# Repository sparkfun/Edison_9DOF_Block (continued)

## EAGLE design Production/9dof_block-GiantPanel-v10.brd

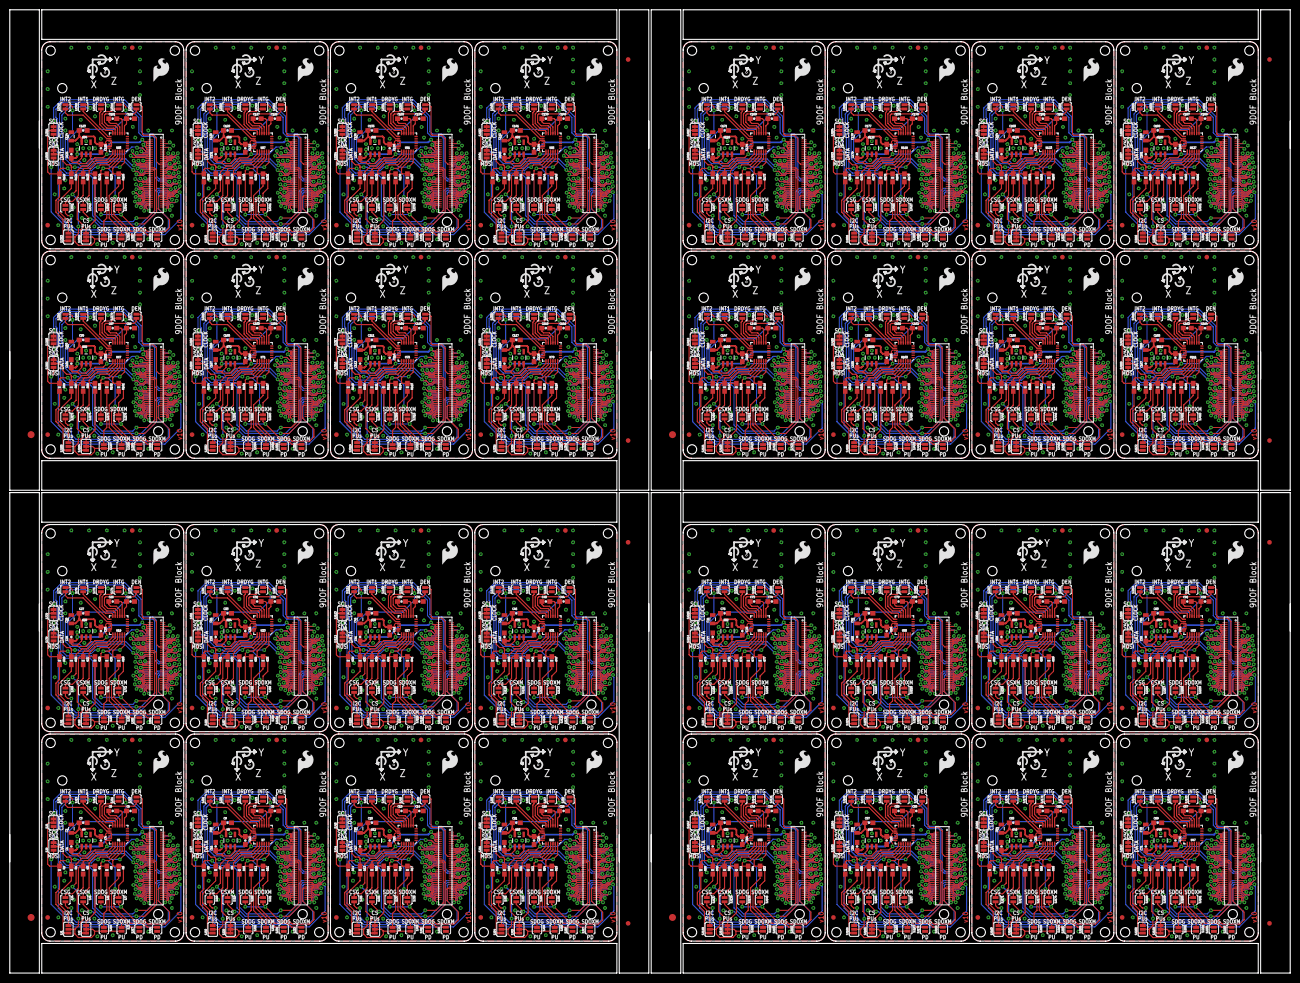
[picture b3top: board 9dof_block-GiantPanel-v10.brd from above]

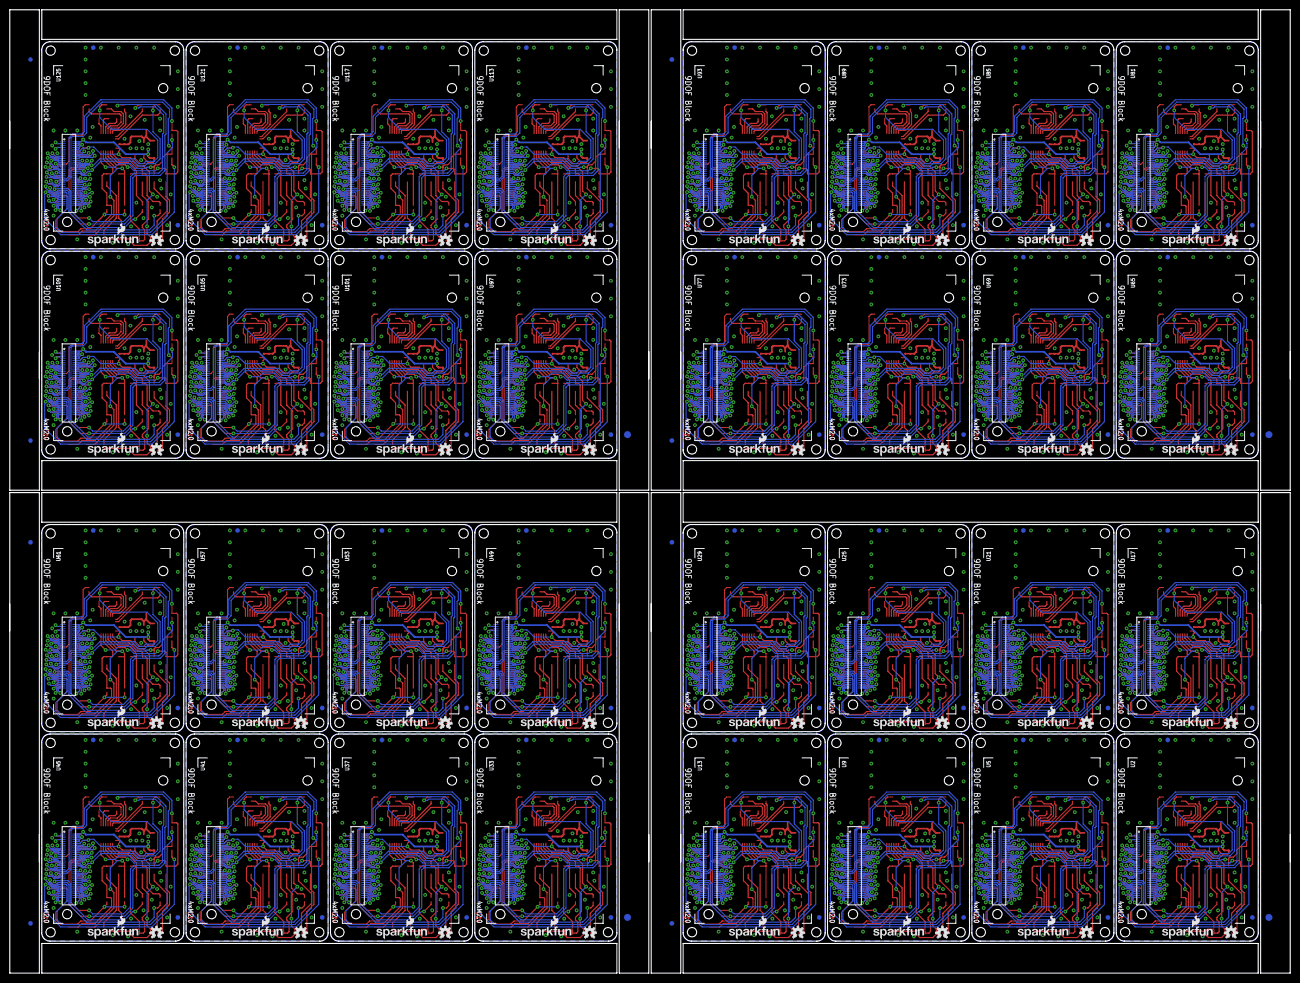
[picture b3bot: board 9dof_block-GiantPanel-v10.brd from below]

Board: 2 copper layers, 274.8 x 206.8 mm, 1304 parts (204 on the bottom side), 2528 nets.

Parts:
C1, C3, C9, C11, C15, C17, C21, C23, C27, C29, C33, C35, C39, C41, C45, C47, C51, C53, C57, C59, C63, C65, C69, C71, C75, C77, C81, C83, C87, C89, C93, C95, C99, C101, C105, C107, C111, C113, C117, C119, C123, C125, C129, C131, C135, C137, C141, C143, C147, C149, C153, C155, C159, C161, C165, C167, C171, C173, C177, C179, C183, C185, C189, C191: 1.0uF; 0603-CAP
C2, C10, C16, C22, C28, C34, C40, C46, C52, C58, C64, C70, C76, C82, C88, C94, C100, C106, C112, C118, C124, C130, C136, C142, C148, C154, C160, C166, C172, C178, C184, C190: 10uF; 0805
C4, C12, C18, C24, C30, C36, C42, C48, C54, C60, C66, C72, C78, C84, C90, C96, C102, C108, C114, C120, C126, C132, C138, C144, C150, C156, C162, C168, C174, C180, C186, C192: 0.1uF; 0603-CAP
C5, C7, C13, C19, C25, C31, C37, C43, C49, C55, C61, C67, C73, C79, C85, C91, C97, C103, C109, C115, C121, C127, C133, C139, C145, C151, C157, C163, C169, C175, C181, C187: 0.22uF; 0603-CAP
C6, C8, C14, C20, C26, C32, C38, C44, C50, C56, C62, C68, C74, C80, C86, C92, C98, C104, C110, C116, C122, C128, C134, C140, C146, C152, C158, C164, C170, C176, C182, C188: 4.7uF; 0603-CAP
E$1, E$2, E$9, E$10, E$15, E$16, E$21, E$22: FIDUCIAL-1.5X3
E$3, E$4, E$5, E$6, E$7, E$8, E$11, E$12, E$13, E$14, E$17, E$18, E$19, E$20, E$23, E$24: FIDUCIAL-1X2
FID1, FID2, FID3, FID4, FID5, FID6, FID7, FID8, FID9, FID10, FID11, FID12, FID13, FID14, FID15, FID16, FID17, FID18, FID19, FID20, FID21, FID22, FID23, FID24, FID25, FID26, FID27, FID28, FID29, FID30, FID31, FID32, FID33, FID34, FID35, FID36, FID37, FID38, FID39, FID40, FID41, FID42, FID43, FID44, FID45, FID46, FID47, FID48, FID49, FID50, FID51, FID52, FID53, FID54, FID55, FID56, FID57, FID58, FID59, FID60, FID61, FID62, FID63, FID64, FID65, FID66, FID67, FID68, FID69, FID70, FID71, FID72, FID73, FID74, FID75, FID76, FID77, FID78, FID79, FID80, FID81, FID82, FID83, FID84, FID85, FID86, FID87, FID88, FID89, FID90, FID91, FID92, FID93, FID94, FID95, FID96, FID97, FID98, FID99, FID100, FID101, FID102, FID103, FID104, FID105, FID106, FID107, FID108, FID109, FID110, FID111, FID112, FID113, FID114, FID115, FID116, FID117, FID118, FID119, FID120, FID121, FID122, FID123, FID124, FID125, FID126, FID127, FID128: FIDUCIAL1X2; FIDUCIAL-1X2
LOGO1, LOGO6, LOGO9, LOGO12, LOGO15, LOGO18, LOGO21, LOGO24, LOGO27, LOGO30, LOGO33, LOGO36, LOGO39, LOGO42, LOGO45, LOGO48, LOGO51, LOGO54, LOGO57, LOGO60, LOGO63, LOGO66, LOGO69, LOGO72, LOGO75, LOGO78, LOGO81, LOGO84, LOGO87, LOGO90, LOGO93, LOGO96: SFE_LOGO_FLAME.2_INCH; SFE_LOGO_FLAME_.2
LOGO2, LOGO4, LOGO7, LOGO10, LOGO13, LOGO16, LOGO19, LOGO22, LOGO25, LOGO28, LOGO31, LOGO34, LOGO37, LOGO40, LOGO43, LOGO46, LOGO49, LOGO52, LOGO55, LOGO58, LOGO61, LOGO64, LOGO67, LOGO70, LOGO73, LOGO76, LOGO79, LOGO82, LOGO85, LOGO88, LOGO91, LOGO94: OSHW-LOGOS; OSHW-LOGO-S
LOGO3, LOGO5, LOGO8, LOGO11, LOGO14, LOGO17, LOGO20, LOGO23, LOGO26, LOGO29, LOGO32, LOGO35, LOGO38, LOGO41, LOGO44, LOGO47, LOGO50, LOGO53, LOGO56, LOGO59, LOGO62, LOGO65, LOGO68, LOGO71, LOGO74, LOGO77, LOGO80, LOGO83, LOGO86, LOGO89, LOGO92, LOGO95: SFE_LOGO_NAME_FLAME.1_INCH; SFE_LOGO_NAME_FLAME_.1
R1, R2, R7, R8, R13, R14, R19, R20, R25, R26, R31, R32, R37, R38, R43, R44, R49, R50, R55, R56, R61, R62, R67, R68, R73, R74, R79, R80, R85, R86, R91, R92, R97, R98, R103, R104, R109, R110, R115, R116, R121, R122, R127, R128, R133, R134, R139, R140, R145, R146, R151, R152, R157, R158, R163, R164, R169, R170, R175, R176, R181, R182, R187, R188: 10K; 0603-RES
R3, R4, R5, R6, R9, R10, R11, R12, R15, R16, R17, R18, R21, R22, R23, R24, R27, R28, R29, R30, R33, R34, R35, R36, R39, R40, R41, R42, R45, R46, R47, R48, R51, R52, R53, R54, R57, R58, R59, R60, R63, R64, R65, R66, R69, R70, R71, R72, R75, R76, R77, R78, R81, R82, R83, R84, R87, R88, R89, R90, R93, R94, R95, R96, R99, R100, R101, R102, R105, R106, R107, R108, R111, R112, R113, R114, R117, R118, R119, R120, R123, R124, R125, R126, R129, R130, R131, R132, R135, R136, R137, R138, R141, R142, R143, R144, R147, R148, R149, R150, R153, R154, R155, R156, R159, R160, R161, R162, R165, R166, R167, R168, R171, R172, R173, R174, R177, R178, R179, R180, R183, R184, R185, R186, R189, R190, R191, R192: 10k; 0603-RES
SJ1, SJ30, SJ47, SJ64, SJ81, SJ98, SJ115, SJ132, SJ149, SJ166, SJ183, SJ200, SJ217, SJ234, SJ251, SJ268, SJ285, SJ302, SJ319, SJ336, SJ353, SJ370, SJ387, SJ404, SJ421, SJ438, SJ455, SJ472, SJ489, SJ506, SJ523, SJ540: JUMPER-PAD-3-NOYES_SILK; PAD-JUMPER-3-NO_YES_SILK
SJ2, SJ29, SJ46, SJ63, SJ80, SJ97, SJ114, SJ131, SJ148, SJ165, SJ182, SJ199, SJ216, SJ233, SJ250, SJ267, SJ284, SJ301, SJ318, SJ335, SJ352, SJ369, SJ386, SJ403, SJ420, SJ437, SJ454, SJ471, SJ488, SJ505, SJ522, SJ539: PAD-JUMPER-3-3OF3_NC_BY_TRACE_YES_SILK_FULL_BOX
SJ3, SJ15, SJ31, SJ32, SJ48, SJ49, SJ65, SJ66, SJ82, SJ83, SJ99, SJ100, SJ116, SJ117, SJ133, SJ134, SJ150, SJ151, SJ167, SJ168, SJ184, SJ185, SJ201, SJ202, SJ218, SJ219, SJ235, SJ236, SJ252, SJ253, SJ269, SJ270, SJ286, SJ287, SJ303, SJ304, SJ320, SJ321, SJ337, SJ338, SJ354, SJ355, SJ371, SJ372, SJ388, SJ389, SJ405, SJ406, SJ422, SJ423, SJ439, SJ440, SJ456, SJ457, SJ473, SJ474, SJ490, SJ491, SJ507, SJ508, SJ524, SJ525, SJ541, SJ542: JUMPER-PAD-2-NC_BY_PASTE; PAD-JUMPER-2-NC_BY_PASTE_YES_SILK
SJ4, SJ5, SJ6, SJ7, SJ10, SJ11, SJ12, SJ13, SJ14, SJ16, SJ17, SJ18, SJ19, SJ20, SJ21, SJ22, SJ23, SJ24, SJ25, SJ26, SJ33, SJ34, SJ35, SJ36, SJ37, SJ38, SJ39, SJ40, SJ41, SJ42, SJ43, SJ50, SJ51, SJ52, SJ53, SJ54, SJ55, SJ56, SJ57, SJ58, SJ59, SJ60, SJ67, SJ68, SJ69, SJ70, SJ71, SJ72, SJ73, SJ74, SJ75, SJ76, SJ77, SJ84, SJ85, SJ86, SJ87, SJ88, SJ89, SJ90, SJ91, SJ92, SJ93, SJ94, SJ101, SJ102, SJ103, SJ104, SJ105, SJ106, SJ107, SJ108, SJ109, SJ110, SJ111, SJ118, SJ119, SJ120, SJ121, SJ122, SJ123, SJ124, SJ125, SJ126, SJ127, SJ128, SJ135, SJ136, SJ137, SJ138, SJ139, SJ140, SJ141, SJ142, SJ143, SJ144, SJ145, SJ152, SJ153, SJ154, SJ155, SJ156, SJ157, SJ158, SJ159, SJ160, SJ161, SJ162, SJ169, SJ170, SJ171, SJ172, SJ173, SJ174, SJ175, SJ176, SJ177, SJ178, SJ179, SJ186, SJ187, SJ188, SJ189, SJ190, SJ191, SJ192, SJ193, SJ194, SJ195, SJ196, SJ203, SJ204, SJ205, SJ206, SJ207, SJ208, SJ209, SJ210, SJ211, SJ212, SJ213, SJ220, SJ221, SJ222, SJ223, SJ224, SJ225, SJ226, SJ227, SJ228, SJ229, SJ230, SJ237, SJ238, SJ239, SJ240, SJ241, SJ242, SJ243, SJ244, SJ245, SJ246, SJ247, SJ254, SJ255, SJ256, SJ257, SJ258, SJ259, SJ260, SJ261, SJ262, SJ263, SJ264, SJ271, SJ272, SJ273, SJ274, SJ275, SJ276, SJ277, SJ278, SJ279, SJ280, SJ281, SJ288, SJ289, SJ290, SJ291, SJ292, SJ293, SJ294, SJ295, SJ296, SJ297, SJ298, SJ305, SJ306, SJ307, SJ308, SJ309, SJ310, SJ311, SJ312, SJ313, SJ314, SJ315, SJ322, SJ323, SJ324, SJ325, SJ326, SJ327, SJ328, SJ329, SJ330, SJ331, SJ332, SJ339, SJ340, SJ341, SJ342, SJ343, SJ344, SJ345, SJ346, SJ347, SJ348, SJ349, SJ356, SJ357, SJ358, SJ359, SJ360, SJ361, SJ362, SJ363, SJ364, SJ365, SJ366, SJ373, SJ374, SJ375, SJ376, SJ377, SJ378, SJ379, SJ380, SJ381, SJ382, SJ383, SJ390, SJ391, SJ392, SJ393, SJ394, SJ395, SJ396, SJ397, SJ398, SJ399, SJ400, SJ407, SJ408, SJ409, SJ410, SJ411, SJ412, SJ413, SJ414, SJ415, SJ416, SJ417, SJ424, SJ425, SJ426, SJ427, SJ428, SJ429, SJ430, SJ431, SJ432, SJ433, SJ434, SJ441, SJ442, SJ443, SJ444, SJ445, SJ446, SJ447, SJ448, SJ449, SJ450, SJ451, SJ458, SJ459, SJ460, SJ461, SJ462, SJ463, SJ464, SJ465, SJ466, SJ467, SJ468, SJ475, SJ476, SJ477, SJ478, SJ479, SJ480, SJ481, SJ482, SJ483, SJ484, SJ485, SJ492, SJ493, SJ494, SJ495, SJ496, SJ497, SJ498, SJ499, SJ500, SJ501, SJ502, SJ509, SJ510, SJ511, SJ512, SJ513, SJ514, SJ515, SJ516, SJ517, SJ518, SJ519, SJ526, SJ527, SJ528, SJ529, SJ530, SJ531, SJ532, SJ533, SJ534, SJ535, SJ536, SJ543, SJ544: JUMPER-PAD-2-NOYES_SILK; PAD-JUMPER-2-NO_YES_SILK
SJ8, SJ9, SJ27, SJ28, SJ44, SJ45, SJ61, SJ62, SJ78, SJ79, SJ95, SJ96, SJ112, SJ113, SJ129, SJ130, SJ146, SJ147, SJ163, SJ164, SJ180, SJ181, SJ197, SJ198, SJ214, SJ215, SJ231, SJ232, SJ248, SJ249, SJ265, SJ266, SJ282, SJ283, SJ299, SJ300, SJ316, SJ317, SJ333, SJ334, SJ350, SJ351, SJ367, SJ368, SJ384, SJ385, SJ401, SJ402, SJ418, SJ419, SJ435, SJ436, SJ452, SJ453, SJ469, SJ470, SJ486, SJ487, SJ503, SJ504, SJ520, SJ521, SJ537, SJ538: JUMPER-PAD-3-2OF3_NC_BY_TRACE_SMALL; PAD-JUMPER-3-2OF3_NC_BY_TRACE_YES_SILK_FULL_BOX
U1, U7, U11, U15, U19, U23, U27, U31, U35, U39, U43, U47, U51, U55, U59, U63, U67, U71, U75, U79, U83, U87, U91, U95, U99, U103, U107, U111, U115, U119, U123, U127: LSM9DS0; LGA-24
U2, U5, U9, U13, U17, U21, U25, U29, U33, U37, U41, U45, U49, U53, U57, U61, U65, U69, U73, U77, U81, U85, U89, U93, U97, U101, U105, U109, U113, U117, U121, U125: EDISON_CONNECTOR_FULLMOUNTING_HOLES; EDISON_DAUGHTER
U3, U6, U10, U14, U18, U22, U26, U30, U34, U38, U42, U46, U50, U54, U58, U62, U66, U70, U74, U78, U82, U86, U90, U94, U98, U102, U106, U110, U114, U118, U122, U126: EDISON_CONNECTOR_FULLHEADER; DF40C-70DP-0.4(51)
U4, U8, U12, U16, U20, U24, U28, U32, U36, U40, U44, U48, U52, U56, U60, U64, U68, U72, U76, U80, U84, U88, U92, U96, U100, U104, U108, U112, U116, U120, U124, U128: MIC52053.3V; SOT23-5

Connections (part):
1.8V: SJ1.2, SJ2.2, SJ3.2, SJ15.2, U1.18, U2.12, U3.12
1.8V1: SJ29.2, SJ30.2, SJ31.2, SJ32.2, U5.12, U6.12, U7.18
1.8V2: SJ46.2, SJ47.2, SJ48.2, SJ49.2, U9.12, U10.12, U11.18
1.8V3: SJ63.2, SJ64.2, SJ65.2, SJ66.2, U13.12, U14.12, U15.18
1.8V4: SJ80.2, SJ81.2, SJ82.2, SJ83.2, U17.12, U18.12, U19.18
1.8V5: SJ97.2, SJ98.2, SJ99.2, SJ100.2, U21.12, U22.12, U23.18
1.8V6: SJ114.2, SJ115.2, SJ116.2, SJ117.2, U25.12, U26.12, U27.18
1.8V7: SJ131.2, SJ132.2, SJ133.2, SJ134.2, U29.12, U30.12, U31.18
1.8V8: SJ148.2, SJ149.2, SJ150.2, SJ151.2, U33.12, U34.12, U35.18
1.8V9: SJ165.2, SJ166.2, SJ167.2, SJ168.2, U37.12, U38.12, U39.18
1.8V10: SJ182.2, SJ183.2, SJ184.2, SJ185.2, U41.12, U42.12, U43.18
1.8V11: SJ199.2, SJ200.2, SJ201.2, SJ202.2, U45.12, U46.12, U47.18
1.8V12: SJ216.2, SJ217.2, SJ218.2, SJ219.2, U49.12, U50.12, U51.18
1.8V13: SJ233.2, SJ234.2, SJ235.2, SJ236.2, U53.12, U54.12, U55.18
1.8V14: SJ250.2, SJ251.2, SJ252.2, SJ253.2, U57.12, U58.12, U59.18
1.8V15: SJ267.2, SJ268.2, SJ269.2, SJ270.2, U61.12, U62.12, U63.18
1.8V16: SJ284.2, SJ285.2, SJ286.2, SJ287.2, U65.12, U66.12, U67.18
1.8V17: SJ301.2, SJ302.2, SJ303.2, SJ304.2, U69.12, U70.12, U71.18
1.8V18: SJ318.2, SJ319.2, SJ320.2, SJ321.2, U73.12, U74.12, U75.18
1.8V19: SJ335.2, SJ336.2, SJ337.2, SJ338.2, U77.12, U78.12, U79.18
1.8V20: SJ352.2, SJ353.2, SJ354.2, SJ355.2, U81.12, U82.12, U83.18
1.8V21: SJ369.2, SJ370.2, SJ371.2, SJ372.2, U85.12, U86.12, U87.18
1.8V22: SJ386.2, SJ387.2, SJ388.2, SJ389.2, U89.12, U90.12, U91.18
1.8V23: SJ403.2, SJ404.2, SJ405.2, SJ406.2, U93.12, U94.12, U95.18
1.8V24: SJ420.2, SJ421.2, SJ422.2, SJ423.2, U97.12, U98.12, U99.18
1.8V25: SJ437.2, SJ438.2, SJ439.2, SJ440.2, U101.12, U102.12, U103.18
1.8V26: SJ454.2, SJ455.2, SJ456.2, SJ457.2, U105.12, U106.12, U107.18
1.8V27: SJ471.2, SJ472.2, SJ473.2, SJ474.2, U109.12, U110.12, U111.18
1.8V28: SJ488.2, SJ489.2, SJ490.2, SJ491.2, U113.12, U114.12, U115.18
1.8V29: SJ505.2, SJ506.2, SJ507.2, SJ508.2, U117.12, U118.12, U119.18
1.8V30: SJ522.2, SJ523.2, SJ524.2, SJ525.2, U121.12, U122.12, U123.18
1.8V31: SJ539.2, SJ540.2, SJ541.2, SJ542.2, U125.12, U126.12, U127.18
3.3V: U2.8, U2.10, U3.8, U3.10
3.3V1: U5.8, U5.10, U6.8, U6.10
3.3V2: U9.8, U9.10, U10.8, U10.10
3.3V3: U13.8, U13.10, U14.8, U14.10
3.3V4: U17.8, U17.10, U18.8, U18.10
3.3V5: U21.8, U21.10, U22.8, U22.10
3.3V6: U25.8, U25.10, U26.8, U26.10
3.3V7: U29.8, U29.10, U30.8, U30.10
3.3V8: U33.8, U33.10, U34.8, U34.10
3.3V9: U37.8, U37.10, U38.8, U38.10
3.3V10: U41.8, U41.10, U42.8, U42.10
3.3V11: U45.8, U45.10, U46.8, U46.10
3.3V12: U49.8, U49.10, U50.8, U50.10
3.3V13: U53.8, U53.10, U54.8, U54.10
3.3V14: U57.8, U57.10, U58.8, U58.10
3.3V15: U61.8, U61.10, U62.8, U62.10
3.3V16: U65.8, U65.10, U66.8, U66.10
3.3V17: U69.8, U69.10, U70.8, U70.10
3.3V18: U73.8, U73.10, U74.8, U74.10
3.3V19: U77.8, U77.10, U78.8, U78.10
3.3V20: U81.8, U81.10, U82.8, U82.10
3.3V21: U85.8, U85.10, U86.8, U86.10
3.3V22: U89.8, U89.10, U90.8, U90.10
3.3V23: U93.8, U93.10, U94.8, U94.10
3.3V24: U97.8, U97.10, U98.8, U98.10
3.3V25: U101.8, U101.10, U102.8, U102.10
3.3V26: U105.8, U105.10, U106.8, U106.10
3.3V27: U109.8, U109.10, U110.8, U110.10
3.3V28: U113.8, U113.10, U114.8, U114.10
3.3V29: U117.8, U117.10, U118.8, U118.10
3.3V30: U121.8, U121.10, U122.8, U122.10
3.3V31: U125.8, U125.10, U126.8, U126.10
3.3V_LOCAL: C2.1, C3.1, C4.1, U1.15, U1.16, U1.17, U4.5
3.3V_LOCAL1: C9.1, C10.1, C12.1, U7.15, U7.16, U7.17, U8.5
3.3V_LOCAL2: C15.1, C16.1, C18.1, U11.15, U11.16, U11.17, U12.5
3.3V_LOCAL3: C21.1, C22.1, C24.1, U15.15, U15.16, U15.17, U16.5
3.3V_LOCAL4: C27.1, C28.1, C30.1, U19.15, U19.16, U19.17, U20.5
3.3V_LOCAL5: C33.1, C34.1, C36.1, U23.15, U23.16, U23.17, U24.5
3.3V_LOCAL6: C39.1, C40.1, C42.1, U27.15, U27.16, U27.17, U28.5
3.3V_LOCAL7: C45.1, C46.1, C48.1, U31.15, U31.16, U31.17, U32.5
3.3V_LOCAL8: C51.1, C52.1, C54.1, U35.15, U35.16, U35.17, U36.5
3.3V_LOCAL9: C57.1, C58.1, C60.1, U39.15, U39.16, U39.17, U40.5
3.3V_LOCAL10: C63.1, C64.1, C66.1, U43.15, U43.16, U43.17, U44.5
3.3V_LOCAL11: C69.1, C70.1, C72.1, U47.15, U47.16, U47.17, U48.5
3.3V_LOCAL12: C75.1, C76.1, C78.1, U51.15, U51.16, U51.17, U52.5
3.3V_LOCAL13: C81.1, C82.1, C84.1, U55.15, U55.16, U55.17, U56.5
3.3V_LOCAL14: C87.1, C88.1, C90.1, U59.15, U59.16, U59.17, U60.5
3.3V_LOCAL15: C93.1, C94.1, C96.1, U63.15, U63.16, U63.17, U64.5
3.3V_LOCAL16: C99.1, C100.1, C102.1, U67.15, U67.16, U67.17, U68.5
3.3V_LOCAL17: C105.1, C106.1, C108.1, U71.15, U71.16, U71.17, U72.5
3.3V_LOCAL18: C111.1, C112.1, C114.1, U75.15, U75.16, U75.17, U76.5
3.3V_LOCAL19: C117.1, C118.1, C120.1, U79.15, U79.16, U79.17, U80.5
3.3V_LOCAL20: C123.1, C124.1, C126.1, U83.15, U83.16, U83.17, U84.5
3.3V_LOCAL21: C129.1, C130.1, C132.1, U87.15, U87.16, U87.17, U88.5
3.3V_LOCAL22: C135.1, C136.1, C138.1, U91.15, U91.16, U91.17, U92.5
3.3V_LOCAL23: C141.1, C142.1, C144.1, U95.15, U95.16, U95.17, U96.5
3.3V_LOCAL24: C147.1, C148.1, C150.1, U99.15, U99.16, U99.17, U100.5
3.3V_LOCAL25: C153.1, C154.1, C156.1, U103.15, U103.16, U103.17, U104.5
3.3V_LOCAL26: C159.1, C160.1, C162.1, U107.15, U107.16, U107.17, U108.5
3.3V_LOCAL27: C165.1, C166.1, C168.1, U111.15, U111.16, U111.17, U112.5
3.3V_LOCAL28: C171.1, C172.1, C174.1, U115.15, U115.16, U115.17, U116.5
3.3V_LOCAL29: C177.1, C178.1, C180.1, U119.15, U119.16, U119.17, U120.5
3.3V_LOCAL30: C183.1, C184.1, C186.1, U123.15, U123.16, U123.17, U124.5
3.3V_LOCAL31: C189.1, C190.1, C192.1, U127.15, U127.16, U127.17, U128.5
CS_G: R3.1, SJ4.1, U1.19
CS_G1: R9.1, SJ18.1, U7.19
CS_G2: R15.1, SJ35.1, U11.19
CS_G3: R21.1, SJ52.1, U15.19
CS_G4: R27.1, SJ69.1, U19.19
CS_G5: R33.1, SJ86.1, U23.19
CS_G6: R39.1, SJ103.1, U27.19
CS_G7: R45.1, SJ120.1, U31.19
CS_G8: R51.1, SJ137.1, U35.19
CS_G9: R57.1, SJ154.1, U39.19
CS_G10: R63.1, SJ171.1, U43.19
CS_G11: R69.1, SJ188.1, U47.19
CS_G12: R75.1, SJ205.1, U51.19
CS_G13: R81.1, SJ222.1, U55.19
CS_G14: R87.1, SJ239.1, U59.19
CS_G15: R93.1, SJ256.1, U63.19
CS_G16: R99.1, SJ273.1, U67.19
CS_G17: R105.1, SJ290.1, U71.19
CS_G18: R111.1, SJ307.1, U75.19
CS_G19: R117.1, SJ324.1, U79.19
CS_G20: R123.1, SJ341.1, U83.19
CS_G21: R129.1, SJ358.1, U87.19
CS_G22: R135.1, SJ375.1, U91.19
CS_G23: R141.1, SJ392.1, U95.19
CS_G24: R147.1, SJ409.1, U99.19
CS_G25: R153.1, SJ426.1, U103.19
CS_G26: R159.1, SJ443.1, U107.19
CS_G27: R165.1, SJ460.1, U111.19
CS_G28: R171.1, SJ477.1, U115.19
CS_G29: R177.1, SJ494.1, U119.19
CS_G30: R183.1, SJ511.1, U123.19
CS_G31: R189.1, SJ528.1, U127.19
CS_XM: R4.1, SJ5.1, U1.20
CS_XM1: R10.1, SJ19.1, U7.20
CS_XM2: R16.1, SJ36.1, U11.20
CS_XM3: R22.1, SJ53.1, U15.20
CS_XM4: R28.1, SJ70.1, U19.20
CS_XM5: R34.1, SJ87.1, U23.20
CS_XM6: R40.1, SJ104.1, U27.20
CS_XM7: R46.1, SJ121.1, U31.20
CS_XM8: R52.1, SJ138.1, U35.20
CS_XM9: R58.1, SJ155.1, U39.20
CS_XM10: R64.1, SJ172.1, U43.20
CS_XM11: R70.1, SJ189.1, U47.20
CS_XM12: R76.1, SJ206.1, U51.20
CS_XM13: R82.1, SJ223.1, U55.20
CS_XM14: R88.1, SJ240.1, U59.20
CS_XM15: R94.1, SJ257.1, U63.20
CS_XM16: R100.1, SJ274.1, U67.20
CS_XM17: R106.1, SJ291.1, U71.20
CS_XM18: R112.1, SJ308.1, U75.20
CS_XM19: R118.1, SJ325.1, U79.20
CS_XM20: R124.1, SJ342.1, U83.20
CS_XM21: R130.1, SJ359.1, U87.20
CS_XM22: R136.1, SJ376.1, U91.20
CS_XM23: R142.1, SJ393.1, U95.20
CS_XM24: R148.1, SJ410.1, U99.20
CS_XM25: R154.1, SJ427.1, U103.20
CS_XM26: R160.1, SJ444.1, U107.20
CS_XM27: R166.1, SJ461.1, U111.20
CS_XM28: R172.1, SJ478.1, U115.20
CS_XM29: R178.1, SJ495.1, U119.20
CS_XM30: R184.1, SJ512.1, U123.20
CS_XM31: R190.1, SJ529.1, U127.20
DCIN: U2.14, U3.14
DCIN1: U5.14, U6.14
DCIN2: U9.14, U10.14
DCIN3: U13.14, U14.14
DCIN4: U17.14, U18.14
DCIN5: U21.14, U22.14
DCIN6: U25.14, U26.14
DCIN7: U29.14, U30.14
DCIN8: U33.14, U34.14
DCIN9: U37.14, U38.14
DCIN10: U41.14, U42.14
DCIN11: U45.14, U46.14
DCIN12: U49.14, U50.14
DCIN13: U53.14, U54.14
DCIN14: U57.14, U58.14
DCIN15: U61.14, U62.14
DCIN16: U65.14, U66.14
DCIN17: U69.14, U70.14
DCIN18: U73.14, U74.14
DCIN19: U77.14, U78.14
DCIN20: U81.14, U82.14
DCIN21: U85.14, U86.14
DCIN22: U89.14, U90.14
DCIN23: U93.14, U94.14
DCIN24: U97.14, U98.14
DCIN25: U101.14, U102.14
DCIN26: U105.14, U106.14
DCIN27: U109.14, U110.14
DCIN28: U113.14, U114.14
DCIN29: U117.14, U118.14
DCIN30: U121.14, U122.14
DCIN31: U125.14, U126.14
DEN_G: SJ10.1, U1.10
DEN_G1: SJ22.1, U7.10
DEN_G2: SJ39.1, U11.10
DEN_G3: SJ56.1, U15.10
DEN_G4: SJ73.1, U19.10
DEN_G5: SJ90.1, U23.10
DEN_G6: SJ107.1, U27.10
DEN_G7: SJ124.1, U31.10
DEN_G8: SJ141.1, U35.10
DEN_G9: SJ158.1, U39.10
DEN_G10: SJ175.1, U43.10
DEN_G11: SJ192.1, U47.10
DEN_G12: SJ209.1, U51.10
DEN_G13: SJ226.1, U55.10
DEN_G14: SJ243.1, U59.10
DEN_G15: SJ260.1, U63.10
DEN_G16: SJ277.1, U67.10
DEN_G17: SJ294.1, U71.10
DEN_G18: SJ311.1, U75.10
DEN_G19: SJ328.1, U79.10
DEN_G20: SJ345.1, U83.10
DEN_G21: SJ362.1, U87.10
DEN_G22: SJ379.1, U91.10
DEN_G23: SJ396.1, U95.10
DEN_G24: SJ413.1, U99.10
DEN_G25: SJ430.1, U103.10
DEN_G26: SJ447.1, U107.10
DEN_G27: SJ464.1, U111.10
DEN_G28: SJ481.1, U115.10
DEN_G29: SJ498.1, U119.10
DEN_G30: SJ515.1, U123.10
DEN_G31: SJ532.1, U127.10
DRDY_G: SJ12.1, U1.12
DRDY_G1: SJ24.1, U7.12
DRDY_G2: SJ41.1, U11.12
DRDY_G3: SJ58.1, U15.12
DRDY_G4: SJ75.1, U19.12
DRDY_G5: SJ92.1, U23.12
DRDY_G6: SJ109.1, U27.12
DRDY_G7: SJ126.1, U31.12
DRDY_G8: SJ143.1, U35.12
DRDY_G9: SJ160.1, U39.12
DRDY_G10: SJ177.1, U43.12
DRDY_G11: SJ194.1, U47.12
DRDY_G12: SJ211.1, U51.12
DRDY_G13: SJ228.1, U55.12
DRDY_G14: SJ245.1, U59.12
DRDY_G15: SJ262.1, U63.12
DRDY_G16: SJ279.1, U67.12
DRDY_G17: SJ296.1, U71.12
DRDY_G18: SJ313.1, U75.12
DRDY_G19: SJ330.1, U79.12
DRDY_G20: SJ347.1, U83.12
DRDY_G21: SJ364.1, U87.12
DRDY_G22: SJ381.1, U91.12
DRDY_G23: SJ398.1, U95.12
DRDY_G24: SJ415.1, U99.12
DRDY_G25: SJ432.1, U103.12
DRDY_G26: SJ449.1, U107.12
DRDY_G27: SJ466.1, U111.12
DRDY_G28: SJ483.1, U115.12
DRDY_G29: SJ500.1, U119.12
DRDY_G30: SJ517.1, U123.12
DRDY_G31: SJ534.1, U127.12
FAULT: U2.19, U3.19
FAULT1: U5.19, U6.19
FAULT2: U9.19, U10.19
FAULT3: U13.19, U14.19
FAULT4: U17.19, U18.19
FAULT5: U21.19, U22.19
FAULT6: U25.19, U26.19
FAULT7: U29.19, U30.19
FAULT8: U33.19, U34.19
FAULT9: U37.19, U38.19
FAULT10: U41.19, U42.19
FAULT11: U45.19, U46.19
FAULT12: U49.19, U50.19
FAULT13: U53.19, U54.19
FAULT14: U57.19, U58.19
FAULT15: U61.19, U62.19
FAULT16: U65.19, U66.19
FAULT17: U69.19, U70.19
FAULT18: U73.19, U74.19
FAULT19: U77.19, U78.19
FAULT20: U81.19, U82.19
FAULT21: U85.19, U86.19
FAULT22: U89.19, U90.19
FAULT23: U93.19, U94.19
FAULT24: U97.19, U98.19
FAULT25: U101.19, U102.19
FAULT26: U105.19, U106.19
FAULT27: U109.19, U110.19
FAULT28: U113.19, U114.19
FAULT29: U117.19, U118.19
FAULT30: U121.19, U122.19
FAULT31: U125.19, U126.19
FW_RCVR: U2.69, U3.69
FW_RCVR1: U5.69, U6.69
FW_RCVR2: U9.69, U10.69
FW_RCVR3: U13.69, U14.69
FW_RCVR4: U17.69, U18.69
FW_RCVR5: U21.69, U22.69
FW_RCVR6: U25.69, U26.69
FW_RCVR7: U29.69, U30.69
FW_RCVR8: U33.69, U34.69
FW_RCVR9: U37.69, U38.69
FW_RCVR10: U41.69, U42.69
FW_RCVR11: U45.69, U46.69
FW_RCVR12: U49.69, U50.69
FW_RCVR13: U53.69, U54.69
FW_RCVR14: U57.69, U58.69
FW_RCVR15: U61.69, U62.69
FW_RCVR16: U65.69, U66.69
FW_RCVR17: U69.69, U70.69
FW_RCVR18: U73.69, U74.69
FW_RCVR19: U77.69, U78.69
FW_RCVR20: U81.69, U82.69
FW_RCVR21: U85.69, U86.69
FW_RCVR22: U89.69, U90.69
FW_RCVR23: U93.69, U94.69
FW_RCVR24: U97.69, U98.69
FW_RCVR25: U101.69, U102.69
FW_RCVR26: U105.69, U106.69
FW_RCVR27: U109.69, U110.69
FW_RCVR28: U113.69, U114.69
FW_RCVR29: U117.69, U118.69
FW_RCVR30: U121.69, U122.69
FW_RCVR31: U125.69, U126.69
GND: C1.2, C2.2, C3.2, C4.2, C6.2, SJ16.1, SJ17.1, U1.2, U1.3, U1.4, U1.5, U1.6, U2.1, U2.5, U2.9, U2.11, U2.13, U2.15, U3.1, U3.5, U3.9, U3.11, U3.13, U3.15, U4.2
GND1: C8.2, C9.2, C10.2, C11.2, C12.2, SJ33.1, SJ34.1, U5.1, U5.5, U5.9, U5.11, U5.13, U5.15, U6.1, U6.5, U6.9, U6.11, U6.13, U6.15, U7.2, U7.3, U7.4, U7.5, U7.6, U8.2
GND2: C14.2, C15.2, C16.2, C17.2, C18.2, SJ50.1, SJ51.1, U9.1, U9.5, U9.9, U9.11, U9.13, U9.15, U10.1, U10.5, U10.9, U10.11, U10.13, U10.15, U11.2, U11.3, U11.4, U11.5, U11.6, U12.2
GND3: C20.2, C21.2, C22.2, C23.2, C24.2, SJ67.1, SJ68.1, U13.1, U13.5, U13.9, U13.11, U13.13, U13.15, U14.1, U14.5, U14.9, U14.11, U14.13, U14.15, U15.2, U15.3, U15.4, U15.5, U15.6, U16.2
GND4: C26.2, C27.2, C28.2, C29.2, C30.2, SJ84.1, SJ85.1, U17.1, U17.5, U17.9, U17.11, U17.13, U17.15, U18.1, U18.5, U18.9, U18.11, U18.13, U18.15, U19.2, U19.3, U19.4, U19.5, U19.6, U20.2
GND5: C32.2, C33.2, C34.2, C35.2, C36.2, SJ101.1, SJ102.1, U21.1, U21.5, U21.9, U21.11, U21.13, U21.15, U22.1, U22.5, U22.9, U22.11, U22.13, U22.15, U23.2, U23.3, U23.4, U23.5, U23.6, U24.2
GND6: C38.2, C39.2, C40.2, C41.2, C42.2, SJ118.1, SJ119.1, U25.1, U25.5, U25.9, U25.11, U25.13, U25.15, U26.1, U26.5, U26.9, U26.11, U26.13, U26.15, U27.2, U27.3, U27.4, U27.5, U27.6, U28.2
GND7: C44.2, C45.2, C46.2, C47.2, C48.2, SJ135.1, SJ136.1, U29.1, U29.5, U29.9, U29.11, U29.13, U29.15, U30.1, U30.5, U30.9, U30.11, U30.13, U30.15, U31.2, U31.3, U31.4, U31.5, U31.6, U32.2
GND8: C50.2, C51.2, C52.2, C53.2, C54.2, SJ152.1, SJ153.1, U33.1, U33.5, U33.9, U33.11, U33.13, U33.15, U34.1, U34.5, U34.9, U34.11, U34.13, U34.15, U35.2, U35.3, U35.4, U35.5, U35.6, U36.2
GND9: C56.2, C57.2, C58.2, C59.2, C60.2, SJ169.1, SJ170.1, U37.1, U37.5, U37.9, U37.11, U37.13, U37.15, U38.1, U38.5, U38.9, U38.11, U38.13, U38.15, U39.2, U39.3, U39.4, U39.5, U39.6, U40.2
GND10: C62.2, C63.2, C64.2, C65.2, C66.2, SJ186.1, SJ187.1, U41.1, U41.5, U41.9, U41.11, U41.13, U41.15, U42.1, U42.5, U42.9, U42.11, U42.13, U42.15, U43.2, U43.3, U43.4, U43.5, U43.6, U44.2
GND11: C68.2, C69.2, C70.2, C71.2, C72.2, SJ203.1, SJ204.1, U45.1, U45.5, U45.9, U45.11, U45.13, U45.15, U46.1, U46.5, U46.9, U46.11, U46.13, U46.15, U47.2, U47.3, U47.4, U47.5, U47.6, U48.2
GND12: C74.2, C75.2, C76.2, C77.2, C78.2, SJ220.1, SJ221.1, U49.1, U49.5, U49.9, U49.11, U49.13, U49.15, U50.1, U50.5, U50.9, U50.11, U50.13, U50.15, U51.2, U51.3, U51.4, U51.5, U51.6, U52.2
GND13: C80.2, C81.2, C82.2, C83.2, C84.2, SJ237.1, SJ238.1, U53.1, U53.5, U53.9, U53.11, U53.13, U53.15, U54.1, U54.5, U54.9, U54.11, U54.13, U54.15, U55.2, U55.3, U55.4, U55.5, U55.6, U56.2
GND14: C86.2, C87.2, C88.2, C89.2, C90.2, SJ254.1, SJ255.1, U57.1, U57.5, U57.9, U57.11, U57.13, U57.15, U58.1, U58.5, U58.9, U58.11, U58.13, U58.15, U59.2, U59.3, U59.4, U59.5, U59.6, U60.2
GND15: C92.2, C93.2, C94.2, C95.2, C96.2, SJ271.1, SJ272.1, U61.1, U61.5, U61.9, U61.11, U61.13, U61.15, U62.1, U62.5, U62.9, U62.11, U62.13, U62.15, U63.2, U63.3, U63.4, U63.5, U63.6, U64.2
GND16: C98.2, C99.2, C100.2, C101.2, C102.2, SJ288.1, SJ289.1, U65.1, U65.5, U65.9, U65.11, U65.13, U65.15, U66.1, U66.5, U66.9, U66.11, U66.13, U66.15, U67.2, U67.3, U67.4, U67.5, U67.6, U68.2
GND17: C104.2, C105.2, C106.2, C107.2, C108.2, SJ305.1, SJ306.1, U69.1, U69.5, U69.9, U69.11, U69.13, U69.15, U70.1, U70.5, U70.9, U70.11, U70.13, U70.15, U71.2, U71.3, U71.4, U71.5, U71.6, U72.2
GND18: C110.2, C111.2, C112.2, C113.2, C114.2, SJ322.1, SJ323.1, U73.1, U73.5, U73.9, U73.11, U73.13, U73.15, U74.1, U74.5, U74.9, U74.11, U74.13, U74.15, U75.2, U75.3, U75.4, U75.5, U75.6, U76.2
GND19: C116.2, C117.2, C118.2, C119.2, C120.2, SJ339.1, SJ340.1, U77.1, U77.5, U77.9, U77.11, U77.13, U77.15, U78.1, U78.5, U78.9, U78.11, U78.13, U78.15, U79.2, U79.3, U79.4, U79.5, U79.6, U80.2
GND20: C122.2, C123.2, C124.2, C125.2, C126.2, SJ356.1, SJ357.1, U81.1, U81.5, U81.9, U81.11, U81.13, U81.15, U82.1, U82.5, U82.9, U82.11, U82.13, U82.15, U83.2, U83.3, U83.4, U83.5, U83.6, U84.2
GND21: C128.2, C129.2, C130.2, C131.2, C132.2, SJ373.1, SJ374.1, U85.1, U85.5, U85.9, U85.11, U85.13, U85.15, U86.1, U86.5, U86.9, U86.11, U86.13, U86.15, U87.2, U87.3, U87.4, U87.5, U87.6, U88.2
GND22: C134.2, C135.2, C136.2, C137.2, C138.2, SJ390.1, SJ391.1, U89.1, U89.5, U89.9, U89.11, U89.13, U89.15, U90.1, U90.5, U90.9, U90.11, U90.13, U90.15, U91.2, U91.3, U91.4, U91.5, U91.6, U92.2
GND23: C140.2, C141.2, C142.2, C143.2, C144.2, SJ407.1, SJ408.1, U93.1, U93.5, U93.9, U93.11, U93.13, U93.15, U94.1, U94.5, U94.9, U94.11, U94.13, U94.15, U95.2, U95.3, U95.4, U95.5, U95.6, U96.2
GND24: C146.2, C147.2, C148.2, C149.2, C150.2, SJ424.1, SJ425.1, U97.1, U97.5, U97.9, U97.11, U97.13, U97.15, U98.1, U98.5, U98.9, U98.11, U98.13, U98.15, U99.2, U99.3, U99.4, U99.5, U99.6, U100.2
GND25: C152.2, C153.2, C154.2, C155.2, C156.2, SJ441.1, SJ442.1, U101.1, U101.5, U101.9, U101.11, U101.13, U101.15, U102.1, U102.5, U102.9, U102.11, U102.13, U102.15, U103.2, U103.3, U103.4, U103.5, U103.6, U104.2
GND26: C158.2, C159.2, C160.2, C161.2, C162.2, SJ458.1, SJ459.1, U105.1, U105.5, U105.9, U105.11, U105.13, U105.15, U106.1, U106.5, U106.9, U106.11, U106.13, U106.15, U107.2, U107.3, U107.4, U107.5, U107.6, U108.2
GND27: C164.2, C165.2, C166.2, C167.2, C168.2, SJ475.1, SJ476.1, U109.1, U109.5, U109.9, U109.11, U109.13, U109.15, U110.1, U110.5, U110.9, U110.11, U110.13, U110.15, U111.2, U111.3, U111.4, U111.5, U111.6, U112.2
GND28: C170.2, C171.2, C172.2, C173.2, C174.2, SJ492.1, SJ493.1, U113.1, U113.5, U113.9, U113.11, U113.13, U113.15, U114.1, U114.5, U114.9, U114.11, U114.13, U114.15, U115.2, U115.3, U115.4, U115.5, U115.6, U116.2
GND29: C176.2, C177.2, C178.2, C179.2, C180.2, SJ509.1, SJ510.1, U117.1, U117.5, U117.9, U117.11, U117.13, U117.15, U118.1, U118.5, U118.9, U118.11, U118.13, U118.15, U119.2, U119.3, U119.4, U119.5, U119.6, U120.2
GND30: C182.2, C183.2, C184.2, C185.2, C186.2, SJ526.1, SJ527.1, U121.1, U121.5, U121.9, U121.11, U121.13, U121.15, U122.1, U122.5, U122.9, U122.11, U122.13, U122.15, U123.2, U123.3, U123.4, U123.5, U123.6, U124.2
GND31: C188.2, C189.2, C190.2, C191.2, C192.2, SJ543.1, SJ544.1, U125.1, U125.5, U125.9, U125.11, U125.13, U125.15, U126.1, U126.5, U126.9, U126.11, U126.13, U126.15, U127.2, U127.3, U127.4, U127.5, U127.6, U128.2
GP1: U5.48, U6.48
GP2: U5.42, U6.42
GP3: SJ26.2, U5.34, U6.34
GP4: SJ25.2, U5.32, U6.32
GP5: SJ24.2, U5.30, U6.30
GP6: SJ23.2, U5.28, U6.28
GP7: U5.26, U6.26
GP8: SJ22.2, U5.25, U6.25
GP9: U5.24, U6.24
GP10: U9.48, U10.48
GP11: U9.42, U10.42
GP12: SJ43.2, U9.34, U10.34
GP12_PWM0: U2.35, U3.35
GP12_PWM1: U5.35, U6.35
GP12_PWM2: U9.35, U10.35
GP12_PWM3: U13.35, U14.35
GP12_PWM4: U17.35, U18.35
GP12_PWM5: U21.35, U22.35
GP12_PWM6: U25.35, U26.35
GP12_PWM7: U29.35, U30.35
GP12_PWM8: U33.35, U34.35
GP12_PWM9: U37.35, U38.35
GP12_PWM10: U41.35, U42.35
GP12_PWM11: U45.35, U46.35
GP12_PWM12: U49.35, U50.35
GP12_PWM13: U53.35, U54.35
GP12_PWM14: U57.35, U58.35
GP12_PWM15: U61.35, U62.35
GP12_PWM16: U65.35, U66.35
GP12_PWM17: U69.35, U70.35
GP12_PWM18: U73.35, U74.35
GP12_PWM19: U77.35, U78.35
GP12_PWM20: U81.35, U82.35
GP12_PWM21: U85.35, U86.35
GP12_PWM22: U89.35, U90.35
GP12_PWM23: U93.35, U94.35
GP12_PWM24: U97.35, U98.35
GP12_PWM25: U101.35, U102.35
GP12_PWM26: U105.35, U106.35
GP12_PWM27: U109.35, U110.35
GP12_PWM28: U113.35, U114.35
GP12_PWM29: U117.35, U118.35
GP12_PWM30: U121.35, U122.35
GP12_PWM31: U125.35, U126.35
GP13: SJ42.2, U9.32, U10.32
GP13_PWM1: U2.33, U3.33
GP13_PWM2: U5.33, U6.33
GP13_PWM3: U9.33, U10.33
GP13_PWM4: U13.33, U14.33
GP13_PWM5: U17.33, U18.33
GP13_PWM6: U21.33, U22.33
GP13_PWM7: U25.33, U26.33
GP13_PWM8: U29.33, U30.33
GP13_PWM9: U33.33, U34.33
GP13_PWM10: U37.33, U38.33
GP13_PWM11: U41.33, U42.33
GP13_PWM12: U45.33, U46.33
GP13_PWM13: U49.33, U50.33
GP13_PWM14: U53.33, U54.33
GP13_PWM15: U57.33, U58.33
GP13_PWM16: U61.33, U62.33
GP13_PWM17: U65.33, U66.33
GP13_PWM18: U69.33, U70.33
GP13_PWM19: U73.33, U74.33
GP13_PWM20: U77.33, U78.33
GP13_PWM21: U81.33, U82.33
GP13_PWM22: U85.33, U86.33
GP13_PWM23: U89.33, U90.33
GP13_PWM24: U93.33, U94.33
GP13_PWM25: U97.33, U98.33
GP13_PWM26: U101.33, U102.33
GP13_PWM27: U105.33, U106.33
GP13_PWM28: U109.33, U110.33
GP13_PWM29: U113.33, U114.33
GP13_PWM30: U117.33, U118.33
GP13_PWM31: U121.33, U122.33
GP13_PWM32: U125.33, U126.33
GP14: U2.48, U3.48
GP15: U2.42, U3.42
GP16: SJ41.2, U9.30, U10.30
GP17: SJ40.2, U9.28, U10.28
GP18: U9.26, U10.26
GP19: SJ39.2, U9.25, U10.25
GP19_I2C_1_SCL: SJ9.3, U2.41, U3.41
GP19_I2C_1_SCL1: SJ28.3, U5.41, U6.41
GP19_I2C_1_SCL2: SJ45.3, U9.41, U10.41
GP19_I2C_1_SCL3: SJ62.3, U13.41, U14.41
GP19_I2C_1_SCL4: SJ79.3, U17.41, U18.41
GP19_I2C_1_SCL5: SJ96.3, U21.41, U22.41
GP19_I2C_1_SCL6: SJ113.3, U25.41, U26.41
GP19_I2C_1_SCL7: SJ130.3, U29.41, U30.41
GP19_I2C_1_SCL8: SJ147.3, U33.41, U34.41
GP19_I2C_1_SCL9: SJ164.3, U37.41, U38.41
GP19_I2C_1_SCL10: SJ181.3, U41.41, U42.41
GP19_I2C_1_SCL11: SJ198.3, U45.41, U46.41
GP19_I2C_1_SCL12: SJ215.3, U49.41, U50.41
GP19_I2C_1_SCL13: SJ232.3, U53.41, U54.41
GP19_I2C_1_SCL14: SJ249.3, U57.41, U58.41
GP19_I2C_1_SCL15: SJ266.3, U61.41, U62.41
GP19_I2C_1_SCL16: SJ283.3, U65.41, U66.41
GP19_I2C_1_SCL17: SJ300.3, U69.41, U70.41
GP19_I2C_1_SCL18: SJ317.3, U73.41, U74.41
GP19_I2C_1_SCL19: SJ334.3, U77.41, U78.41
GP19_I2C_1_SCL20: SJ351.3, U81.41, U82.41
GP19_I2C_1_SCL21: SJ368.3, U85.41, U86.41
GP19_I2C_1_SCL22: SJ385.3, U89.41, U90.41
GP19_I2C_1_SCL23: SJ402.3, U93.41, U94.41
GP19_I2C_1_SCL24: SJ419.3, U97.41, U98.41
GP19_I2C_1_SCL25: SJ436.3, U101.41, U102.41
GP19_I2C_1_SCL26: SJ453.3, U105.41, U106.41
GP19_I2C_1_SCL27: SJ470.3, U109.41, U110.41
GP19_I2C_1_SCL28: SJ487.3, U113.41, U114.41
GP19_I2C_1_SCL29: SJ504.3, U117.41, U118.41
GP19_I2C_1_SCL30: SJ521.3, U121.41, U122.41
GP19_I2C_1_SCL31: SJ538.3, U125.41, U126.41
GP20: U9.24, U10.24
GP20_I2C_1_SDA: SJ8.3, U2.43, U3.43
GP20_I2C_1_SDA1: SJ27.3, U5.43, U6.43
GP20_I2C_1_SDA2: SJ44.3, U9.43, U10.43
GP20_I2C_1_SDA3: SJ61.3, U13.43, U14.43
GP20_I2C_1_SDA4: SJ78.3, U17.43, U18.43
GP20_I2C_1_SDA5: SJ95.3, U21.43, U22.43
GP20_I2C_1_SDA6: SJ112.3, U25.43, U26.43
GP20_I2C_1_SDA7: SJ129.3, U29.43, U30.43
GP20_I2C_1_SDA8: SJ146.3, U33.43, U34.43
GP20_I2C_1_SDA9: SJ163.3, U37.43, U38.43
GP20_I2C_1_SDA10: SJ180.3, U41.43, U42.43
GP20_I2C_1_SDA11: SJ197.3, U45.43, U46.43
GP20_I2C_1_SDA12: SJ214.3, U49.43, U50.43
GP20_I2C_1_SDA13: SJ231.3, U53.43, U54.43
GP20_I2C_1_SDA14: SJ248.3, U57.43, U58.43
GP20_I2C_1_SDA15: SJ265.3, U61.43, U62.43
GP20_I2C_1_SDA16: SJ282.3, U65.43, U66.43
GP20_I2C_1_SDA17: SJ299.3, U69.43, U70.43
GP20_I2C_1_SDA18: SJ316.3, U73.43, U74.43
GP20_I2C_1_SDA19: SJ333.3, U77.43, U78.43
GP20_I2C_1_SDA20: SJ350.3, U81.43, U82.43
GP20_I2C_1_SDA21: SJ367.3, U85.43, U86.43
GP20_I2C_1_SDA22: SJ384.3, U89.43, U90.43
GP20_I2C_1_SDA23: SJ401.3, U93.43, U94.43
GP20_I2C_1_SDA24: SJ418.3, U97.43, U98.43
GP20_I2C_1_SDA25: SJ435.3, U101.43, U102.43
GP20_I2C_1_SDA26: SJ452.3, U105.43, U106.43
GP20_I2C_1_SDA27: SJ469.3, U109.43, U110.43
GP20_I2C_1_SDA28: SJ486.3, U113.43, U114.43
GP20_I2C_1_SDA29: SJ503.3, U117.43, U118.43
GP20_I2C_1_SDA30: SJ520.3, U121.43, U122.43
GP20_I2C_1_SDA31: SJ537.3, U125.43, U126.43
GP21: U13.48, U14.48
GP22: U13.42, U14.42
GP23: SJ60.2, U13.34, U14.34
GP24: SJ59.2, U13.32, U14.32
GP25: SJ58.2, U13.30, U14.30
GP26: SJ57.2, U13.28, U14.28
GP27: U13.26, U14.26
GP27_I2C_6_SCL: U2.45, U3.45
GP27_I2C_6_SCL1: U5.45, U6.45
GP27_I2C_6_SCL2: U9.45, U10.45
GP27_I2C_6_SCL3: U13.45, U14.45
GP27_I2C_6_SCL4: U17.45, U18.45
GP27_I2C_6_SCL5: U21.45, U22.45
GP27_I2C_6_SCL6: U25.45, U26.45
GP27_I2C_6_SCL7: U29.45, U30.45
GP27_I2C_6_SCL8: U33.45, U34.45
GP27_I2C_6_SCL9: U37.45, U38.45
GP27_I2C_6_SCL10: U41.45, U42.45
GP27_I2C_6_SCL11: U45.45, U46.45
GP27_I2C_6_SCL12: U49.45, U50.45
GP27_I2C_6_SCL13: U53.45, U54.45
GP27_I2C_6_SCL14: U57.45, U58.45
GP27_I2C_6_SCL15: U61.45, U62.45
GP27_I2C_6_SCL16: U65.45, U66.45
GP27_I2C_6_SCL17: U69.45, U70.45
GP27_I2C_6_SCL18: U73.45, U74.45
GP27_I2C_6_SCL19: U77.45, U78.45
GP27_I2C_6_SCL20: U81.45, U82.45
GP27_I2C_6_SCL21: U85.45, U86.45
GP27_I2C_6_SCL22: U89.45, U90.45
GP27_I2C_6_SCL23: U93.45, U94.45
GP27_I2C_6_SCL24: U97.45, U98.45
GP27_I2C_6_SCL25: U101.45, U102.45
GP27_I2C_6_SCL26: U105.45, U106.45
GP27_I2C_6_SCL27: U109.45, U110.45
GP27_I2C_6_SCL28: U113.45, U114.45
GP27_I2C_6_SCL29: U117.45, U118.45
GP27_I2C_6_SCL30: U121.45, U122.45
GP27_I2C_6_SCL31: U125.45, U126.45
GP28: SJ56.2, U13.25, U14.25
GP28_I2C_6_SDA: U2.47, U3.47
GP28_I2C_6_SDA1: U5.47, U6.47
GP28_I2C_6_SDA2: U9.47, U10.47
GP28_I2C_6_SDA3: U13.47, U14.47
GP28_I2C_6_SDA4: U17.47, U18.47
GP28_I2C_6_SDA5: U21.47, U22.47
GP28_I2C_6_SDA6: U25.47, U26.47
GP28_I2C_6_SDA7: U29.47, U30.47
GP28_I2C_6_SDA8: U33.47, U34.47
GP28_I2C_6_SDA9: U37.47, U38.47
GP28_I2C_6_SDA10: U41.47, U42.47
GP28_I2C_6_SDA11: U45.47, U46.47
GP28_I2C_6_SDA12: U49.47, U50.47
GP28_I2C_6_SDA13: U53.47, U54.47
GP28_I2C_6_SDA14: U57.47, U58.47
GP28_I2C_6_SDA15: U61.47, U62.47
GP28_I2C_6_SDA16: U65.47, U66.47
GP28_I2C_6_SDA17: U69.47, U70.47
GP28_I2C_6_SDA18: U73.47, U74.47
GP28_I2C_6_SDA19: U77.47, U78.47
GP28_I2C_6_SDA20: U81.47, U82.47
GP28_I2C_6_SDA21: U85.47, U86.47
GP28_I2C_6_SDA22: U89.47, U90.47
GP28_I2C_6_SDA23: U93.47, U94.47
GP28_I2C_6_SDA24: U97.47, U98.47
GP28_I2C_6_SDA25: U101.47, U102.47
GP28_I2C_6_SDA26: U105.47, U106.47
GP28_I2C_6_SDA27: U109.47, U110.47
GP28_I2C_6_SDA28: U113.47, U114.47
GP28_I2C_6_SDA29: U117.47, U118.47
GP28_I2C_6_SDA30: U121.47, U122.47
GP28_I2C_6_SDA31: U125.47, U126.47
GP29: U13.24, U14.24
GP30: U17.48, U18.48
GP31: U17.42, U18.42
GP32: SJ77.2, U17.34, U18.34
GP33: SJ76.2, U17.32, U18.32
GP34: SJ75.2, U17.30, U18.30
GP35: SJ74.2, U17.28, U18.28
GP36: U17.26, U18.26
GP37: SJ73.2, U17.25, U18.25
GP38: U17.24, U18.24
GP39: U21.48, U22.48
GP40: U21.42, U22.42
GP40_I2S_2_CLK: U2.52, U3.52
GP40_I2S_2_CLK1: U5.52, U6.52
GP40_I2S_2_CLK2: U9.52, U10.52
GP40_I2S_2_CLK3: U13.52, U14.52
GP40_I2S_2_CLK4: U17.52, U18.52
GP40_I2S_2_CLK5: U21.52, U22.52
GP40_I2S_2_CLK6: U25.52, U26.52
GP40_I2S_2_CLK7: U29.52, U30.52
GP40_I2S_2_CLK8: U33.52, U34.52
GP40_I2S_2_CLK9: U37.52, U38.52
GP40_I2S_2_CLK10: U41.52, U42.52
GP40_I2S_2_CLK11: U45.52, U46.52
GP40_I2S_2_CLK12: U49.52, U50.52
GP40_I2S_2_CLK13: U53.52, U54.52
GP40_I2S_2_CLK14: U57.52, U58.52
GP40_I2S_2_CLK15: U61.52, U62.52
GP40_I2S_2_CLK16: U65.52, U66.52
GP40_I2S_2_CLK17: U69.52, U70.52
GP40_I2S_2_CLK18: U73.52, U74.52
GP40_I2S_2_CLK19: U77.52, U78.52
GP40_I2S_2_CLK20: U81.52, U82.52
GP40_I2S_2_CLK21: U85.52, U86.52
GP40_I2S_2_CLK22: U89.52, U90.52
GP40_I2S_2_CLK23: U93.52, U94.52
GP40_I2S_2_CLK24: U97.52, U98.52
GP40_I2S_2_CLK25: U101.52, U102.52
GP40_I2S_2_CLK26: U105.52, U106.52
GP40_I2S_2_CLK27: U109.52, U110.52
GP40_I2S_2_CLK28: U113.52, U114.52
GP40_I2S_2_CLK29: U117.52, U118.52
GP40_I2S_2_CLK30: U121.52, U122.52
GP40_I2S_2_CLK31: U125.52, U126.52
GP41: SJ94.2, U21.34, U22.34
GP41_I2S_2_FS: U2.54, U3.54
GP41_I2S_2_FS1: U5.54, U6.54
GP41_I2S_2_FS2: U9.54, U10.54
GP41_I2S_2_FS3: U13.54, U14.54
GP41_I2S_2_FS4: U17.54, U18.54
GP41_I2S_2_FS5: U21.54, U22.54
GP41_I2S_2_FS6: U25.54, U26.54
GP41_I2S_2_FS7: U29.54, U30.54
GP41_I2S_2_FS8: U33.54, U34.54
GP41_I2S_2_FS9: U37.54, U38.54
GP41_I2S_2_FS10: U41.54, U42.54
GP41_I2S_2_FS11: U45.54, U46.54
GP41_I2S_2_FS12: U49.54, U50.54
GP41_I2S_2_FS13: U53.54, U54.54
GP41_I2S_2_FS14: U57.54, U58.54
GP41_I2S_2_FS15: U61.54, U62.54
GP41_I2S_2_FS16: U65.54, U66.54
GP41_I2S_2_FS17: U69.54, U70.54
GP41_I2S_2_FS18: U73.54, U74.54
GP41_I2S_2_FS19: U77.54, U78.54
GP41_I2S_2_FS20: U81.54, U82.54
GP41_I2S_2_FS21: U85.54, U86.54
GP41_I2S_2_FS22: U89.54, U90.54
GP41_I2S_2_FS23: U93.54, U94.54
GP41_I2S_2_FS24: U97.54, U98.54
GP41_I2S_2_FS25: U101.54, U102.54
GP41_I2S_2_FS26: U105.54, U106.54
GP41_I2S_2_FS27: U109.54, U110.54
GP41_I2S_2_FS28: U113.54, U114.54
GP41_I2S_2_FS29: U117.54, U118.54
GP41_I2S_2_FS30: U121.54, U122.54
GP41_I2S_2_FS31: U125.54, U126.54
GP42: SJ93.2, U21.32, U22.32
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
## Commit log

2014-08-06 Created initial schematic
2014-08-07 Updated to new template. Initial component placement.
2014-08-07 v01 board layout complete
2014-08-08 Added LDO
2014-08-08 Changed to 1.8V IO and added 4x 2-way jumpers for address select.
2014-08-09 Re-did power section to include LDO. Added 4x 2-way jumpers to layout for pullups/pulldowns.
2014-08-09 Added fiducials and moved ver text on layout. Moved address table near pullups/pulldowns on schematic.
2014-08-09 Added second side fiducials.
2014-08-11 Connected SDO_XM and SDO_G together to SPI2_RX on Edison.
2014-08-11 Fixed hanging wire from LDO and added LDO chip name to schematic.
2014-08-12 Changed silk name from Edzzanine 9DOF to just 9DOF.
2014-08-20 Updated README with a better description.
2014-09-24 Added DCIN pin Corrected Header footprint Modified Name of board cleaned up units and added units cleaned up copper fills
2014-10-16 Rev to 10, fix gnd and pwr, text
2014-10-17 Paste to trace jumpers, edit packages
2014-10-17 Rename files
2014-10-17 Ready for reds, v10
2014-10-21 moved fid
2014-10-21 created v10 panels
2016-01-20 Updates to Readme and License file
2016-01-20 Update directory name
